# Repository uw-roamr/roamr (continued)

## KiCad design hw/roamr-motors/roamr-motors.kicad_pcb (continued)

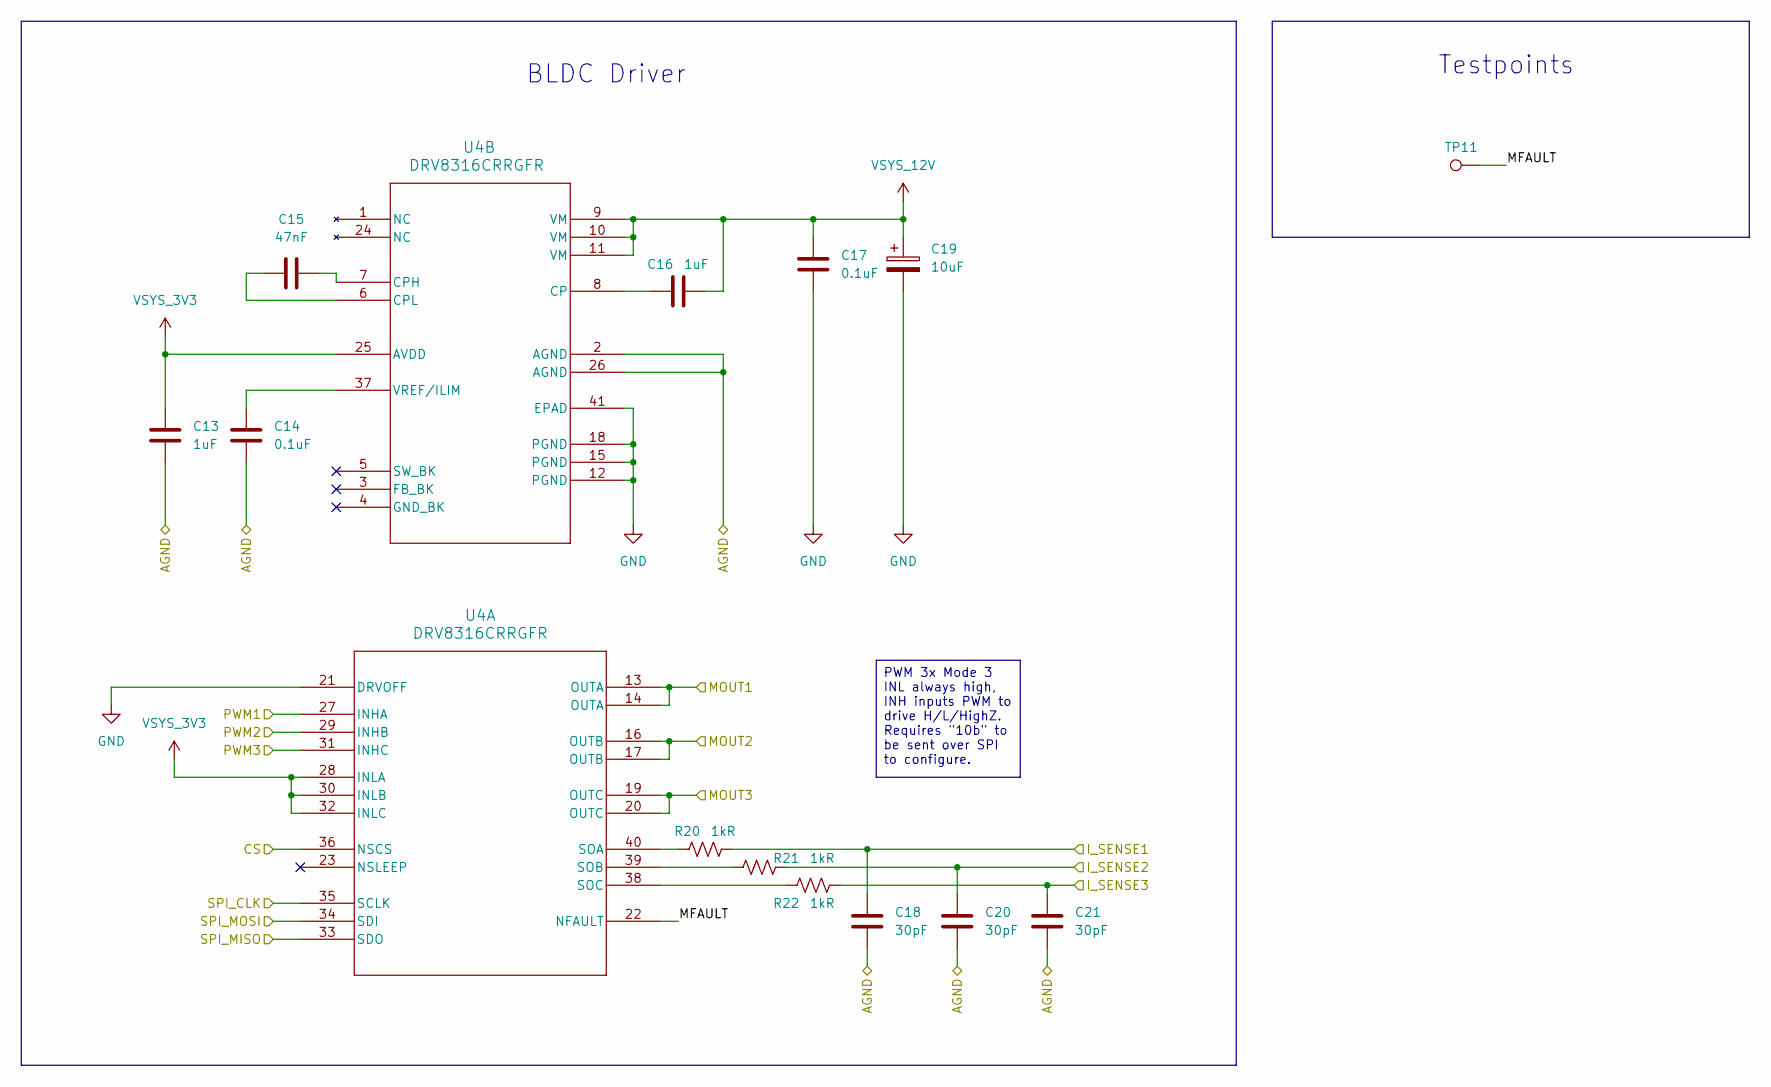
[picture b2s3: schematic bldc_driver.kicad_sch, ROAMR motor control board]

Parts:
C13, C16: 1uF; C_0603_1608Metric
C14, C17: 0.1uF; C_0603_1608Metric
C15: 47nF; C_0603_1608Metric
C18, C20, C21: 30pF; C_0603_1608Metric
C19: 10uF; RVT1E100M0405
R20, R21, R22: 1kR; R_0603_1608Metric
TP11: TestPoint; TestPoint_Pad_D1.5mm
U4: DRV8316CRRGFR; VQFN40_RGF_TEX; Manufacturer_Part_Number DRV8316CRRGFR

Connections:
/BLDC Driver 1/AGND: C13.2, C14.2, C18.2, C20.2, C21.2, U4.2 (AGND), U4.26 (AGND); also elsewhere on the board
/BLDC Driver 1/MFAULT: TP11.1, U4.22 (NFAULT)
/CS_DR_M1: U4.36 (NSCS); also elsewhere on the board
/ISENSE1_M1: C18.1, R20.2; also elsewhere on the board
/ISENSE2_M1: C20.1, R21.2; also elsewhere on the board
/ISENSE3_M1: C21.1, R22.2; also elsewhere on the board
/MOUT1_M1: U4.13 (OUTA), U4.14 (OUTA); also elsewhere on the board
/MOUT2_M1: U4.16 (OUTB), U4.17 (OUTB); also elsewhere on the board
/MOUT3_M1: U4.19 (OUTC), U4.20 (OUTC); also elsewhere on the board
/PWM1_M1: U4.27 (INHA); also elsewhere on the board
/PWM2_M1: U4.29 (INHB); also elsewhere on the board
/PWM3_M1: U4.31 (INHC); also elsewhere on the board
/SPI_CLK: U4.35 (SCLK); also elsewhere on the board
/SPI_MISO: U4.33 (SDO); also elsewhere on the board
/SPI_MOSI: U4.34 (SDI); also elsewhere on the board
GND: C17.2, C19.2, U4.12 (PGND), U4.15 (PGND), U4.18 (PGND), U4.21 (DRVOFF), U4.41 (EPAD); also elsewhere on the board
unnamed: R20.1, U4.40 (SOA)
unnamed: R21.1, U4.39 (SOB)
unnamed: R22.1, U4.38 (SOC)
unnamed: C16.1, U4.8 (CP)
unnamed: C15.2, U4.7 (CPH)
unnamed: C15.1, U4.6 (CPL)
unnamed: C14.1, U4.37 (VREF/ILIM)
VSYS_3V3: C13.1, U4.25 (AVDD), U4.28 (INLA), U4.30 (INLB), U4.32 (INLC); also elsewhere on the board
VSYS_12V: C16.2, C17.1, C19.1, U4.9 (VM), U4.10 (VM), U4.11 (VM); also elsewhere on the board

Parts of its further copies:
C22, C25: 1uF; C_0603_1608Metric
C23, C26: 0.1uF; C_0603_1608Metric
C24: 47nF; C_0603_1608Metric
C27, C29, C30: 30pF; C_0603_1608Metric
C28: 10uF; RVT1E100M0405
R23, R24, R25: 1kR; R_0603_1608Metric
TP12: TestPoint; TestPoint_Pad_D1.5mm
U5: DRV8316CRRGFR; VQFN40_RGF_TEX; Manufacturer_Part_Number DRV8316CRRGFR

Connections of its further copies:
/BLDC Driver 2/AGND: C22.2, C23.2, C27.2, C29.2, C30.2, U5.2 (AGND), U5.26 (AGND); also elsewhere on the board
/BLDC Driver 2/MFAULT: TP12.1, U5.22 (NFAULT)
/CS_DR_M2: U5.36 (NSCS); also elsewhere on the board
/ISENSE1_M2: C27.1, R23.2; also elsewhere on the board
/ISENSE2_M2: C29.1, R24.2; also elsewhere on the board
/ISENSE3_M2: C30.1, R25.2; also elsewhere on the board
/MOUT1_M2: U5.13 (OUTA), U5.14 (OUTA); also elsewhere on the board
/MOUT2_M2: U5.16 (OUTB), U5.17 (OUTB); also elsewhere on the board
/MOUT3_M2: U5.19 (OUTC), U5.20 (OUTC); also elsewhere on the board
/PWM1_M2: U5.27 (INHA); also elsewhere on the board
/PWM2_M2: U5.29 (INHB); also elsewhere on the board
/PWM3_M2: U5.31 (INHC); also elsewhere on the board
/SPI_CLK: U5.35 (SCLK); also elsewhere on the board
/SPI_MISO: U5.33 (SDO); also elsewhere on the board
/SPI_MOSI: U5.34 (SDI); also elsewhere on the board
GND: C26.2, C28.2, U5.12 (PGND), U5.15 (PGND), U5.18 (PGND), U5.21 (DRVOFF), U5.41 (EPAD); also elsewhere on the board
unnamed: R23.1, U5.40 (SOA)
unnamed: R24.1, U5.39 (SOB)
unnamed: R25.1, U5.38 (SOC)
unnamed: C25.1, U5.8 (CP)
unnamed: C24.2, U5.7 (CPH)
unnamed: C24.1, U5.6 (CPL)
unnamed: C23.1, U5.37 (VREF/ILIM)
VSYS_3V3: C22.1, U5.25 (AVDD), U5.28 (INLA), U5.30 (INLB), U5.32 (INLC); also elsewhere on the board
VSYS_12V: C25.2, C26.1, C28.1, U5.9 (VM), U5.10 (VM), U5.11 (VM); also elsewhere on the board

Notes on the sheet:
Testpoints
BLDC Driver
PWM 3x Mode 3 INL always high, INH inputs PWM to drive H/L/HighZ. Requires "10b" to be sent over SPI to configure.

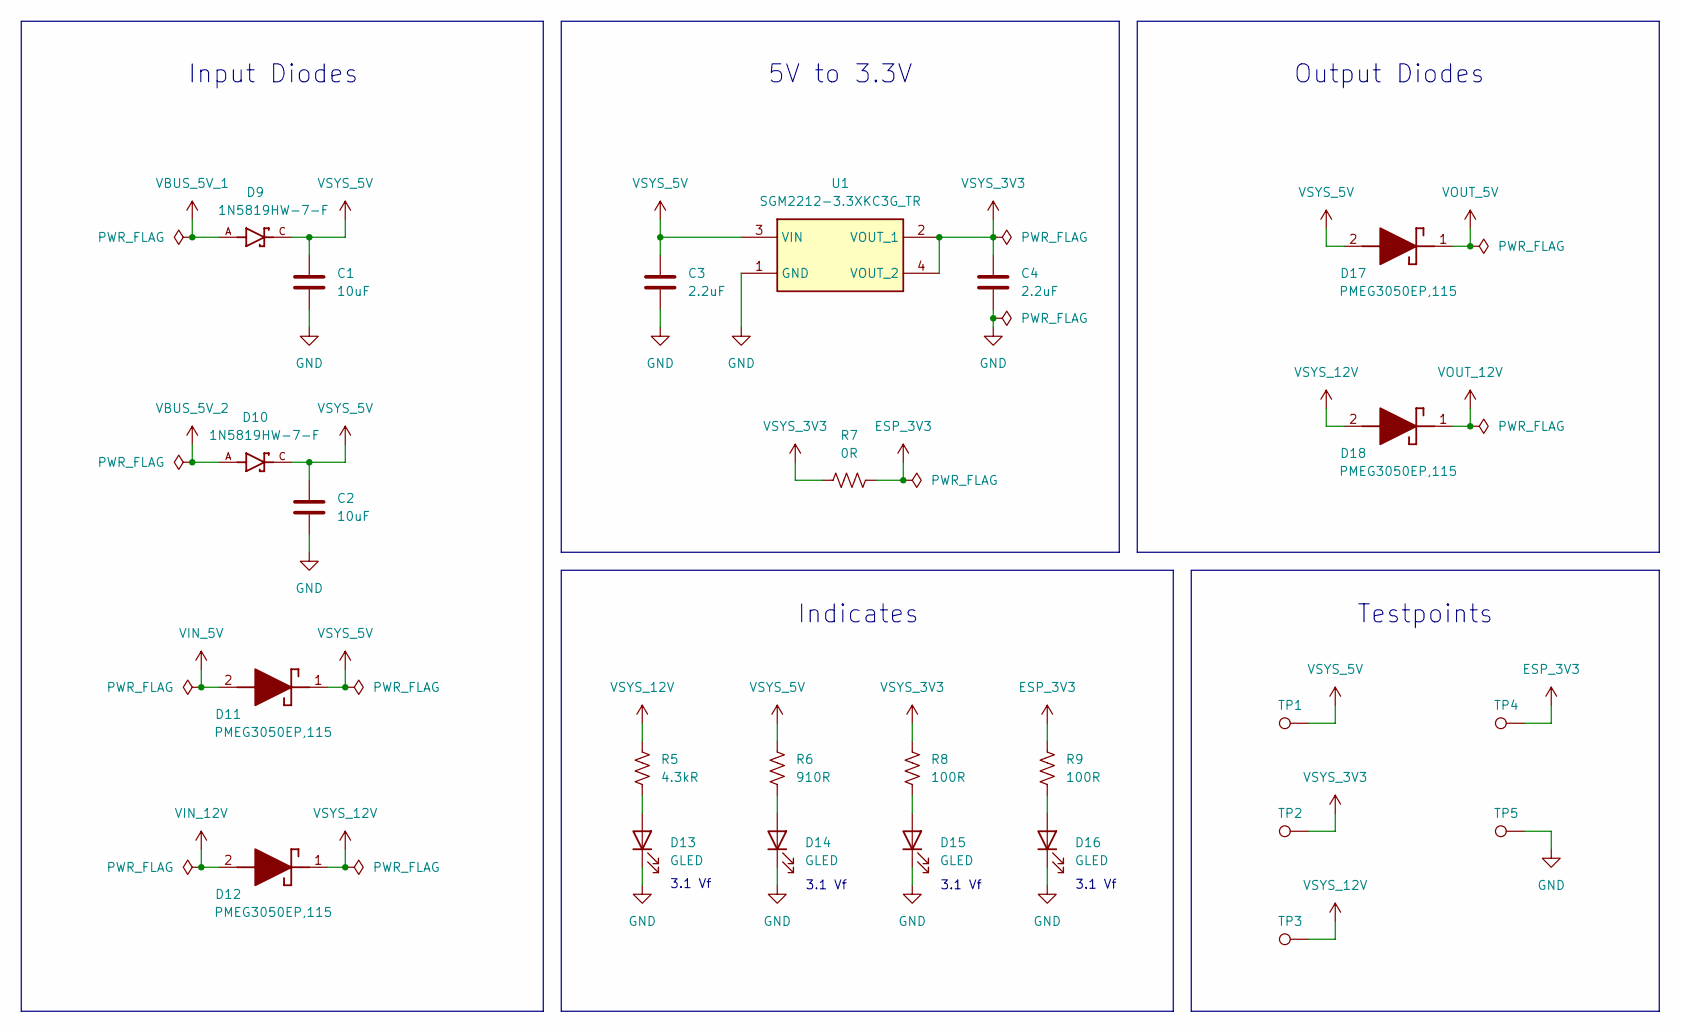
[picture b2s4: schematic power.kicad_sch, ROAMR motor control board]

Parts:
C1, C2: 10uF; C_0603_1608Metric
C3, C4: 2.2uF; C_0603_1608Metric
D9, D10: 1N5819HW-7-F; SOD3715X145N; PARTREV 18-2
D11, D12, D17, D18: PMEG3050EP,115; PMEG3050EP115; Mouser Part Number 771-PMEG3050EP115
D13, D14, D15, D16: GLED; LEDC1608X70N
R5: 4.3kR; R_0603_1608Metric
R6: 910R; R_0603_1608Metric
R7: 0R; R_0603_1608Metric
R8, R9: 100R; R_0603_1608Metric
TP1, TP2, TP3, TP4: TestPoint; TestPoint_Pad_D1.5mm
TP5: TestPoint; TestPoint_Keystone_5005-5009_Compact
U1: SGM2212-3.3XKC3G_TR; SOT230P700X180-4N; Manufacturer_Part_Number SGM2212-3.3XKC3G/TR

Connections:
ESP_3V3: R7.2, R9.1, TP4.1; also elsewhere on the board
GND: C1.2, C2.2, C3.2, C4.2, D13.1 (K), D14.1 (K), D15.1 (K), D16.1 (K), TP5.1, U1.1 (GND); also elsewhere on the board
unnamed: D13.2 (A), R5.2
unnamed: D14.2 (A), R6.2
unnamed: D15.2 (A), R8.2
unnamed: D16.2 (A), R9.2
VBUS_5V_1: D9.A; also elsewhere on the board
VBUS_5V_2: D10.A; also elsewhere on the board
VIN_5V: D11.2 (A); also elsewhere on the board
VIN_12V: D12.2 (A); also elsewhere on the board
VOUT_5V: D17.1 (K); also elsewhere on the board
VOUT_12V: D18.1 (K); also elsewhere on the board
VSYS_3V3: C4.1, R7.1, R8.1, TP2.1, U1.2 (VOUT_1), U1.4 (VOUT_2); also elsewhere on the board
VSYS_5V: C1.1, C2.1, C3.1, D9.C, D10.C, D11.1 (K), D17.2 (A), R6.1, TP1.1, U1.3 (VIN)
VSYS_12V: D12.1 (K), D18.2 (A), R5.1, TP3.1; also elsewhere on the board

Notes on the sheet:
Input Diodes
3.1 Vf
Output Diodes
Testpoints
5V to 3.3V
Indicates

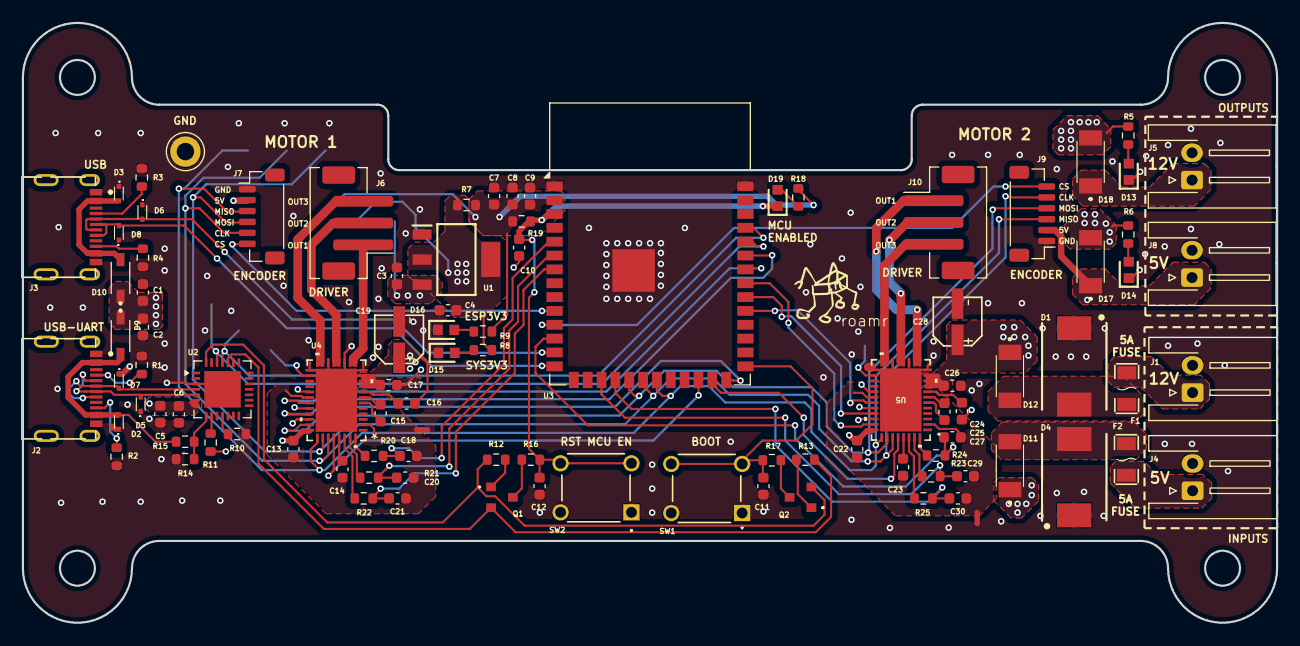
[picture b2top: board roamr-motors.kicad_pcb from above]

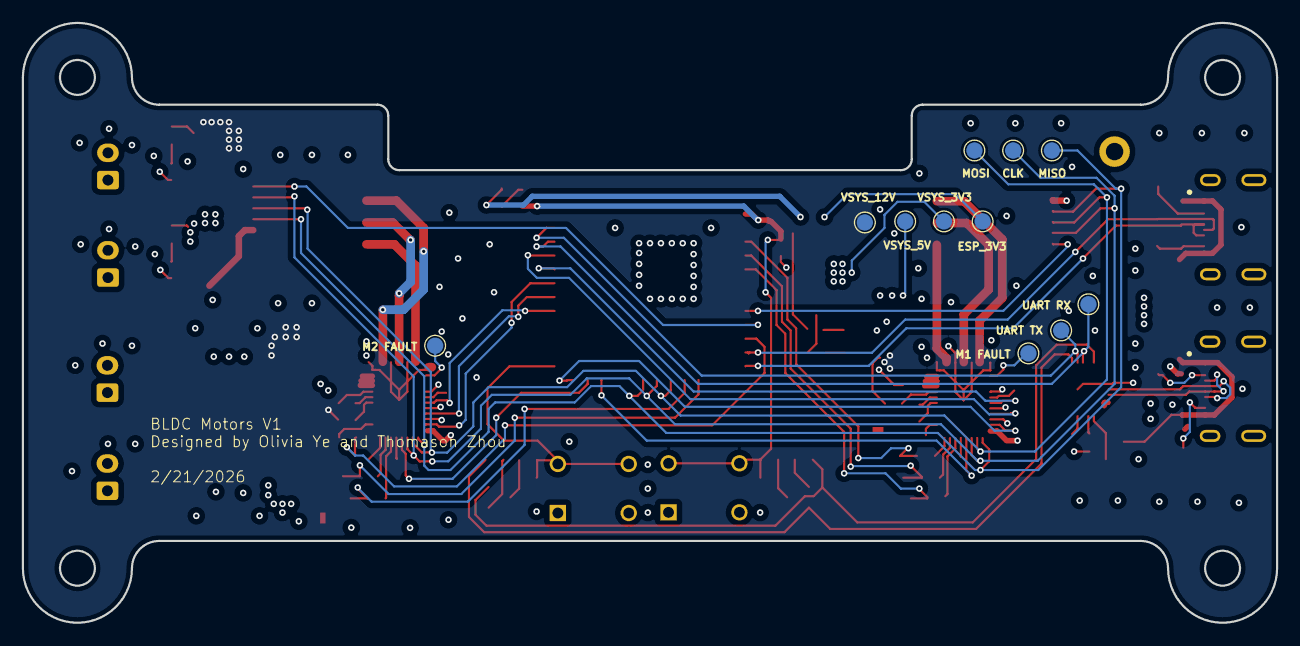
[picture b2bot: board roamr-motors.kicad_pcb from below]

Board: 4 copper layers, 115.0 x 55.0 mm, 109 parts (11 on the bottom side), 82 nets.

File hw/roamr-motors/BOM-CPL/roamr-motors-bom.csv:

Reference,Qty,Value,Manufacturer_Part_Number,DNP,Exclude from BOM,Exclude from Board,Footprint,Datasheet
"C1,C2,C8",3,10uF,,,,,Capacitor_SMD:C_0603_1608Metric,~
"C3,C4",2,2.2uF,,,,,Capacitor_SMD:C_0603_1608Metric,~
C5,1,4.7uF,,,,,Capacitor_SMD:C_0603_1608Metric,~
"C6,C9,C14,C17,C23,C26",6,0.1uF,,,,,Capacitor_SMD:C_0603_1608Metric,~
C7,1,22uF,,,,,Capacitor_SMD:C_0603_1608Metric,~
"C10,C13,C16,C22,C25",5,1uF,,,,,Capacitor_SMD:C_0603_1608Metric,~
"C11,C12",2,0.1uF,,DNP,,,Capacitor_SMD:C_0603_1608Metric,~
"C15,C24",2,47nF,,,,,Capacitor_SMD:C_0603_1608Metric,~
"C18,C20,C21,C27,C29,C30",6,30pF,,,,,Capacitor_SMD:C_0603_1608Metric,~
"C19,C28",2,10uF,,,,,RVT1E100M0405:RVT1E100M0405,~
"D1,D4",2,SMLJ13CA-R,SMLJ13CA-R,,,,SMLJ13CA-R:DIOM7959X262N,~
"D2,D3,D5,D6,D7,D8",6,LESD5D5.0CT1G,LESD5D5.0CT1G,,,,LESD5D5.0CT1G:LESD5D50CT1G,~
"D9,D10",2,1N5819HW-7-F,1N5819HW-7-F,,,,1N5819HW_7_F:SOD3715X145N,
"D11,D12,D17,D18",4,"PMEG3050EP,115","PMEG3050EP,115",,,,PMEG3050EP:PMEG3050EP115,https://assets.nexperia.com/documents/data-sheet/PMEG3050EP.pdf
"D13,D14,D15,D16",4,GLED,KT-0603G,,,,KT-0603:LEDC1608X70N,~
D19,1,RLED,KT-0603R,,,,KT-0603:LEDC1608X70N,~
"F1,F2",2,0466005.NRHF,0466005.NRHF,,,,0466005:F1206,https://lcsc.com/product-detail/Surface-Mount-Fuses_Littelfu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
"J1,J4,J5,J8",4,JST_XH_S2B-XH-A-1,JST_XH_S2B-XH-A-1,,,,Connector_JST:JST_XH_S2B-XH-A-1_1x02_P2.50mm_Horizontal,~
"J2,J3",2,USB4215-03-A,USB4215-03-A,,,,USB4215_03_A:CONN_8p94X6p5X3p16_12L_GCC,USB4215-03-A
"J6,J9",2,JST_PH_B3B-PH-SM4-TB,JST_PH_B3B-PH-SM4-TB,,,,Connector_JST:JST_PH_B3B-PH-SM4-TB_1x03-1MP_P2.00mm_Vertical,~
"J7,J10",2,JST_SH_BM06B-SRSS-TB,JST_SH_BM06B-SRSS-TB,,,,Connector_JST:JST_SH_BM06B-SRSS-TB_1x06-1MP_P1.00mm_Vertical,~
"NT1,NT2",2,NetTie_2,,,Excluded from BOM,,NetTie:NetTie-2_SMD_Pad0.5mm,~
"Q1,Q2",2,L8050QLT1G,L8050QLT1G,,,,L8050QLT1G:L8050QLT1G,https://datasheet.datasheetarchive.com/originals/distributor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
"R1,R2,R3,R4",4,5.1kR,,,,,Resistor_SMD:R_0603_1608Metric,~
R5,1,4.3kR,,,,,Resistor_SMD:R_0603_1608Metric,~
R6,1,910R,,,,,Resistor_SMD:R_0603_1608Metric,~
"R7,R16,R17",3,0R,,,,,Resistor_SMD:R_0603_1608Metric,~
"R8,R9",2,100R,,,,,Resistor_SMD:R_0603_1608Metric,~
R10,1,47.5k,,DNP,,,Resistor_SMD:R_0603_1608Metric,~
R11,1,1k,,,,,Resistor_SMD:R_0603_1608Metric,~
"R12,R13,R19",3,10kR,,,,,Resistor_SMD:R_0603_1608Metric,~
R14,1,22.1k,,,,,Resistor_SMD:R_0603_1608Metric,~
R15,1,47.5k,,,,,Resistor_SMD:R_0603_1608Metric,~
R18,1,430R,,,,,Resistor_SMD:R_0603_1608Metric,~
"R20,R21,R22,R23,R24,R25",6,1kR,,,,,Resistor_SMD:R_0603_1608Metric,~
"SW1,SW2",2,1825910-6,1825910-6,,,,1825910_6:SW4_1825910-B_TEC,1825910-6
"TP1,TP2,TP3,TP4,TP6,TP7,TP8,TP9,TP10,TP11,TP12",11,TestPoint,,,,,TestPoint:TestPoint_Pad_D1.5mm,~
TP5,1,TestPoint,5005-5009,,,,TestPoint:TestPoint_Keystone_5005-5009_Compact,~
U1,1,SGM2212-3.3XKC3G_TR,SGM2212-3.3XKC3G/TR,,,,SGM2212-3.3XKC3G_TR:SOT230P700X180-4N,http://cn.sg-micro.com/uploads/soft/20220506/1651835177.pdf
U2,1,CP2102N-A02-GQFN28,CP2102N-A02-GQFN28,,,,Package_DFN_QFN:QFN-28-1EP_5x5mm_P0.5mm_EP3.35x3.35mm,https://www.silabs.com/documents/public/data-sheets/cp2102n-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
U3,1,ESP32-S3-WROOM-1,ESP32-S3-WROOM-1,,,,RF_Module:ESP32-S3-WROOM-1,https://www.espressif.com/sites/default/files/documentation/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
"U4,U5",2,DRV8316CRRGFR,DRV8316CRRGFR,,,,DRV8316CRRGFR:VQFN40_RGF_TEX,https://www.ti.com/lit/gpn/drv8316c

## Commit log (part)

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2025-11-04 Precommit
2025-11-04 Setup pre-commit github workflow
2025-11-05 Added all metrics and settings page
2025-11-08 Working wasm interaction, swift calling wasm
2025-11-08 remove realityfoundation
2025-11-09 localization wasm instructions
2025-11-16 Update pre-commit
2025-11-16 Fix some pre-commit
2025-11-16 Update pre-commit hooks
2025-11-19 Added new wamr but doesnt run yet
2025-11-21 Temp for olivia
2025-11-23 BLDC version CAD
2025-11-23 Fix double declaration issue
2025-11-23 Log timestamps effectively
2025-11-23 Final touches
2025-11-23 BLE options to write with and without response (#6)
2025-11-24 Add LidarCameraManager without AVFoundation
2025-11-24 Limit rate of logging thread (#12)
2025-11-24 Update project to integrate foc
2025-11-24 Deps and sdkconfig
2026-01-09 Add AVFoundation code for configuring capture session, todo: callback for updating data
2026-01-09 Implement LidarCameraManager
2026-01-17 Added depth view along with a visual overhaul of app.
2026-01-18 Added point cloud view along with websocket page fix
2026-01-18 Update data structures
2026-01-18 Remove duplicates
2026-01-18 Tz/lidar camera (#15)
    * Add AVFoundation code for configuring capture session, todo: callback for updating data
    * Add copy logic with dirty flag
    * Implement LidarCameraManager
    * Remove unneeded print
    * Added depth view along with a visual overhaul of app.
    * Added point cloud view along with websocket page fix
2026-01-18 Fixed video feed
2026-01-18 Fixed video stream rebase conflicts
2026-01-19 Add buck
2026-01-19 reorganizing to roamr-power
2026-01-19 cleanup from moving files
2026-01-19 Access lidar camera data in WASM
2026-01-20 mostly finished power, probably need a bit of drawing cleanup, for schematic
2026-01-20 WIP ESP32 and USB UART
2026-01-21 removing unnecesarry things
2026-01-21 Added wasm viewer/downloader/uploader to web and ios sides. Currently just has user pass login
2026-01-22 swift-side multithreading
2026-01-22 Add rerun logging
2026-01-22 Added new wasm website and integration with ios with working upload and download, only sign in with google sso
2026-01-23 Fixed problem with black screen and rate limiting
2026-01-24 picked the BOM and added two more indicator LEDs for the 12V and 5V rails
2026-01-28 Add USB-UART, USB receptacles, ESP32-S3-WROOM-1, switches. TODO: 5V_3V3 LDO, BLDC drivers, encoder SPI, connectors
2026-01-28 Add series resistors
2026-01-31 lidar undistortion, lidar-camera color, phone pose
2026-02-03 minimal wasm motor commands drive_percent and drive_for
2026-02-03 motor bar graph rerun viz
2026-02-04 cleanup and improved lidar
2026-02-04 rerun video stream and infra cleanup
2026-02-06 WASM motors (#22)
    * Access lidar camera data in WASM
    * WASM bundle search
    * swift-side multithreading
    * Log 3d points
    * Add rerun logging
    * Add ui update
2026-02-06 Refactor WASM architecture
2026-02-06 Add corner detection shell
2026-02-06 portrait-native
2026-02-06 camera frame mapping
2026-02-07 filtered yaw from IMU
2026-02-08 FAST wip
2026-02-09 Log raw IMU
2026-02-09 Reorganize
2026-02-09 Add initial IMU calibration
2026-02-11 Bump pillow from 12.1.0 to 12.1.1 in /tools
    Bumps [pillow](https://github.com/python-pillow/Pillow) from 12.1.0 to 12.1.1.
    - [Release notes](https://github.com/python-pillow/Pillow/releases)
    - [Changelog](https://github.com/python-pillow/Pillow/blob/main/CHANGES.rst)
    - [Commits](https://github.com/python-pillow/Pillow/compare/12.1.0...12.1.1)
    ---
    updated-dependencies:
2026-02-12 Add utils
2026-02-12 Bump pillow from 12.1.0 to 12.1.1 in /tools (#23)
2026-02-12 Update slam main with pose logs
2026-02-12 Rotation only preintegration
2026-02-12 Missing rotate by 90 x
2026-02-12 IMU and map
2026-02-12 Update map pose
2026-02-12 Update IMU calib to block mapping
2026-02-14 pcb schematic and layout updated
2026-02-14 final changes
2026-02-14 just moving around the usb connectors
2026-02-14 removing some wasm file
2026-02-16 added all footprints, starting layout properly
2026-02-17 some more layout
2026-02-19 layout done except i need to add two fuses
2026-02-19 some silkscreen stuff
2026-02-21 final edits
2026-02-21 outputs
2026-02-21 outputs again
2026-02-21 final
2026-02-28 safe rerun shutdown
2026-02-28 Bump rollup from 4.55.2 to 4.59.0 in /wasm-hub
    Bumps [rollup](https://github.com/rollup/rollup) from 4.55.2 to 4.59.0.
    - [Release notes](https://github.com/rollup/rollup/releases)
    - [Changelog](https://github.com/rollup/rollup/blob/master/CHANGELOG.md)
    - [Commits](https://github.com/rollup/rollup/compare/v4.55.2...v4.59.0)
    ---
    updated-dependencies:
2026-03-01 Bump minimatch in /wasm-hub
    Bumps and [minimatch](https://github.com/isaacs/minimatch). These dependencies needed to be updated together.
    Updates `minimatch` from 3.1.2 to 3.1.5
    - [Changelog](https://github.com/isaacs/minimatch/blob/main/changelog.md)
    - [Commits](https://github.com/isaacs/minimatch/compare/v3.1.2...v3.1.5)
    Updates `minimatch` from 9.0.5 to 9.0.9
    - [Changelog](https://github.com/isaacs/minimatch/blob/main/changelog.md)
2026-03-01 Don't let warnings fail build
2026-03-01 Add instructions for components
2026-03-01 Add BLE packet for wheel odometry
2026-03-01 Python 3.14 black
2026-03-01 Update iOS app
2026-03-01 wheel encoder
2026-03-02 Adjust build
2026-03-02 multithread init
2026-03-02 Update readme (#30)
2026-03-03 bt manager fix
2026-03-03 Update with ports for linux
2026-03-03 various updates
2026-03-03 stripped down firmware
2026-03-03 flip right encoder
2026-03-03 Strip down firmware (#34)
2026-03-03 Refactor to use wheel odom rotation as source of truth
2026-03-03 prefer esp32_c6 again
2026-03-03 Double
2026-03-03 map with translation trail
2026-03-03 decent inner loop?
2026-03-04 goal point and plan (outer pid untested)
2026-03-04 corrected orientation, still a bit slow
2026-03-04 Remove unused log_lc
2026-03-04 WASM odom mapping (#37)
    * Refactor to use wheel odom rotation as source of truth
    * map with translation trail
    * Use poseSE3d for translation/rotation
    ---------
2026-03-04 debugging
2026-03-04 Remove cpp from swift project
2026-03-04 pwm enable no matter what
2026-03-04 Add skeleton
2026-03-04 nsleep
2026-03-05 trying
2026-03-05 color filtered 3d points pink
2026-03-05 trying more
2026-03-05 Add debug code for future reference
2026-03-05 Story of my life
2026-03-05 Word
2026-03-05 Checkpoint
2026-03-05 Update ESP32 firmware for S3 board with DRV8316R motor drivers (#42)
2026-03-08 Update global state machine
2026-03-08 Increase max threads to 8
2026-03-08 Driving
2026-03-08 Cleanup logging
2026-03-08 Ok mapping on init
2026-03-08 don't log motors
2026-03-08 ahhhhh
2026-03-08 10-15 controller
2026-03-08 Resolve
2026-03-08 Fix lidar reading to not require timestamp change
2026-03-08 Cleanup mapping
2026-03-08 Fast map
2026-03-09 Fix sensor refresh rate issue
2026-03-09 Increase max range of map
2026-03-09 Add fused option
2026-03-09 4x90 v1
2026-03-09 Refactor map
2026-03-09 4x90 with uncommented control thread
2026-03-09 Rename file
2026-03-09 Decouple visualization logic from mapping
2026-03-09 TUNED 4x90
2026-03-09 Revert "Integrate out of range points to boundary too"
    This reverts commit 956e9f8b361db211a644d4745c66af1710856b54.
2026-03-09 add hardcode demo and revert fucked map
2026-03-09 Use gyro for rotation when fusing odom
2026-03-09 Snapshot
2026-03-09 Non demo planner
2026-03-09 revision-based pipeline
2026-03-10 wasm programs and teleop fix and lower threshold
2026-03-10 teleop hold issue fixed?
2026-03-10 top width fix
2026-03-10 down syndrome
2026-03-10 better pan + zoom, refresh public files
2026-03-10 rebase on main
2026-03-10 fix webpage duplication
2026-03-10 Fixed cert issue and some extra files inclued in wrong target
2026-03-10 autonomy v2 (#44)
2026-03-10 2sec lidar warmup
2026-03-10 A lot of changes
2026-03-10 Fix map bug: initialize odom before initializing map
2026-03-10 Costmap
2026-03-11 Pre commit
2026-03-11 autonomy v3 (#45)
2026-03-11 fix the merge
2026-03-11 fix bugs on map
2026-03-11 map drawing speedups
2026-03-11 simplified planner
2026-03-11 Build abseil-cpp and protobuf 34.0 for WASI
2026-03-11 Remove a lot of third_party
2026-03-12 PRETTY GOOOOD
2026-03-12 layers, fast but screwed recorder maybe
2026-03-12 slight improvements
2026-03-13 Layers (#47)
2026-03-15 better webpage
2026-03-16 Power PCB V1 (#19)
2026-03-16 Update README (#48)
2026-03-16 fixed
    olivia's edits
    reorganizing to roamr-power
    cleanup from moving files
    mostly finished power, probably need a bit of drawing cleanup, for schematic
    fixed after nathan's rereview
    removing unnecesarry things
2026-03-16 Remove cpp files from build
2026-03-17 Decouple lidar camera
2026-03-17 Optimize critical path (RGB conversion was taking over 500 ms
2026-03-17 fruit map attempt 1
2026-03-17 Slightly healthier inference
2026-03-17 20 fps AV
2026-03-17 Vectorize ml preprocessing to reduce critical path to forward inference
2026-03-17 Run ML from html page
2026-03-17 Upload wasm from websocket
2026-03-17 Increase robustness of websocket tooling
2026-03-17 Auto sync stream with wasm run
2026-03-18 Try high confidence depth only
2026-03-18 Semantic object detection v1
2026-03-19 better websocket?
2026-03-19 teasdasd
2026-03-19 Rebuilt
2026-03-19 Tune PID heading
2026-03-19 Update rendering on browser side
2026-03-19 Show planned path
2026-03-19 Change vis
2026-03-19 Profile control
2026-03-19 Render frontiers
2026-03-20 Add safety buffer
2026-03-20 Fix frontier replan bug
2026-03-20 Incremental frontier expansion
2026-03-20 Increase heap and stack size
2026-03-20 Fix bug where planning freezes
2026-03-20 Good
2026-03-20 Checkpoint, but slow
2026-03-20 undoing settings changes
2026-03-20 Map update threshold
2026-03-20 Stable low noise
2026-03-20 Planner clearance
2026-03-20 Map occlusion
2026-03-20 Smear fix, ground height
2026-03-20 Up threshold of hits for confirmation
2026-03-20 Fix goal loop
2026-03-20 Minimum 5, kOccupancy 7, precompute frontiers
2026-03-20 -1m min
2026-03-20 Increase costmap inflation
2026-03-20 Faster
2026-03-20 ml2 hybrid
2026-03-20 Faster Vis + Old Planner Hybrid (#53)
2026-03-26 Bump picomatch from 4.0.3 to 4.0.4 in /wasm-hub
    Bumps [picomatch](https://github.com/micromatch/picomatch) from 4.0.3 to 4.0.4.
    - [Release notes](https://github.com/micromatch/picomatch/releases)
    - [Changelog](https://github.com/micromatch/picomatch/blob/master/CHANGELOG.md)
    - [Commits](https://github.com/micromatch/picomatch/compare/4.0.3...4.0.4)
    ---
    updated-dependencies:
2026-03-26 Bump requests from 2.32.5 to 2.33.0 in /WASM/ml
    Bumps [requests](https://github.com/psf/requests) from 2.32.5 to 2.33.0.
    - [Release notes](https://github.com/psf/requests/releases)
    - [Changelog](https://github.com/psf/requests/blob/main/HISTORY.md)
    - [Commits](https://github.com/psf/requests/compare/v2.32.5...v2.33.0)
    ---
    updated-dependencies:
2026-04-06 Bump vite from 7.3.1 to 7.3.2 in /wasm-hub
    Bumps [vite](https://github.com/vitejs/vite/tree/HEAD/packages/vite) from 7.3.1 to 7.3.2.
    - [Release notes](https://github.com/vitejs/vite/releases)
    - [Changelog](https://github.com/vitejs/vite/blob/v7.3.2/packages/vite/CHANGELOG.md)
    - [Commits](https://github.com/vitejs/vite/commits/v7.3.2/packages/vite)
    ---
    updated-dependencies:
2026-04-13 Bump pillow from 12.1.1 to 12.2.0 in /tools
    Bumps [pillow](https://github.com/python-pillow/Pillow) from 12.1.1 to 12.2.0.
    - [Release notes](https://github.com/python-pillow/Pillow/releases)
    - [Changelog](https://github.com/python-pillow/Pillow/blob/main/CHANGES.rst)
    - [Commits](https://github.com/python-pillow/Pillow/compare/12.1.1...12.2.0)
    ---
    updated-dependencies:
2026-04-17 Bump protobufjs from 7.5.4 to 7.5.5 in /wasm-hub
    Bumps [protobufjs](https://github.com/protobufjs/protobuf.js) from 7.5.4 to 7.5.5.
    - [Release notes](https://github.com/protobufjs/protobuf.js/releases)
    - [Changelog](https://github.com/protobufjs/protobuf.js/blob/master/CHANGELOG.md)
    - [Commits](https://github.com/protobufjs/protobuf.js/compare/protobufjs-v7.5.4...protobufjs-v7.5.5)
    ---
    updated-dependencies:
2026-05-13 Bump @protobufjs/utf8 from 1.1.0 to 1.1.1 in /wasm-hub
    Bumps [@protobufjs/utf8](https://github.com/dcodeIO/protobuf.js) from 1.1.0 to 1.1.1.
    - [Release notes](https://github.com/dcodeIO/protobuf.js/releases)
    - [Changelog](https://github.com/protobufjs/protobuf.js/blob/master/CHANGELOG.md)
    - [Commits](https://github.com/dcodeIO/protobuf.js/compare/protobufjs-cli-v1.1.0...protobufjs-cli-v1.1.1)
    ---
    updated-dependencies:
